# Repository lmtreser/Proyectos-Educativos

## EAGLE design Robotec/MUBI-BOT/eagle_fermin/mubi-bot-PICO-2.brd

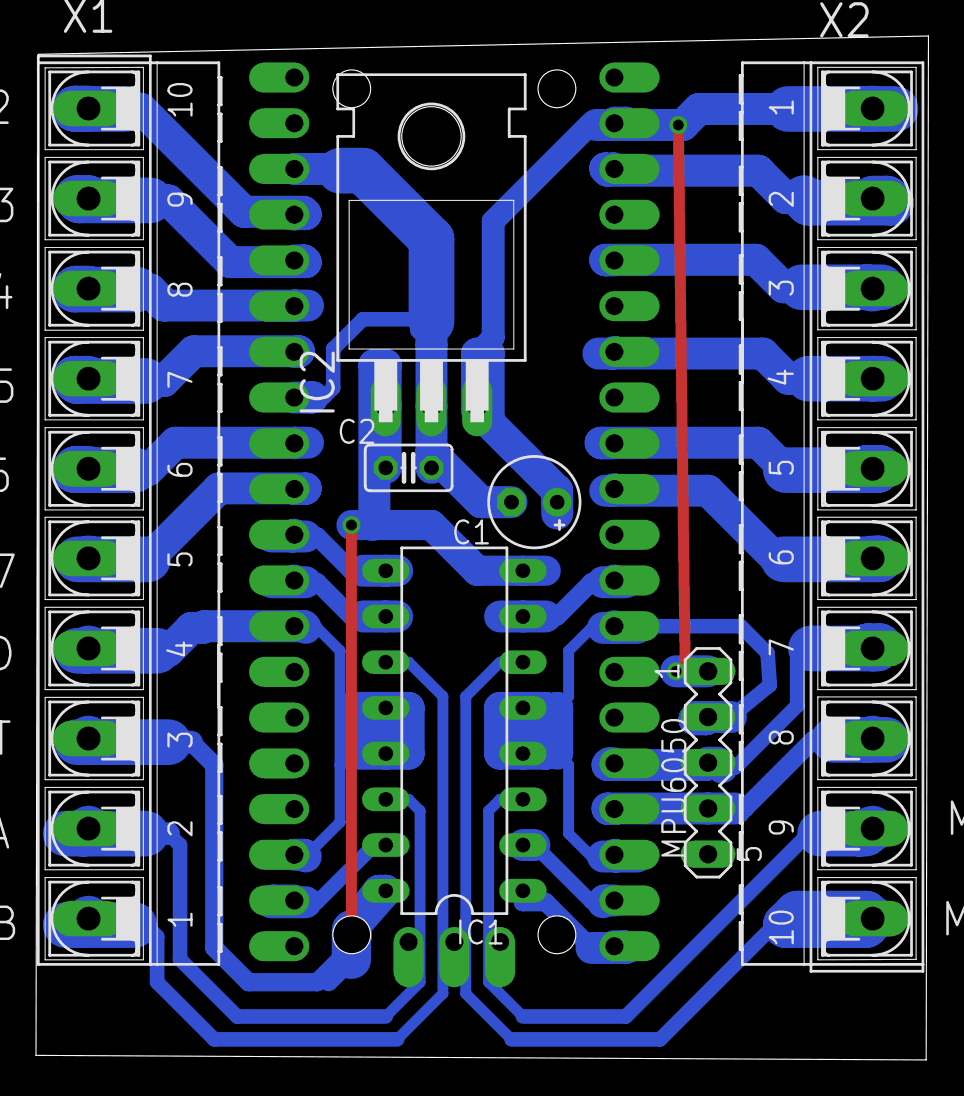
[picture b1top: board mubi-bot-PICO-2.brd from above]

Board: 2 copper layers, 49.6 x 56.9 mm, 8 parts (0 on the bottom side), 25 nets.

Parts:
C1: 10uF/16V; E2,5-5
C2: 100nF; C025-025X050
IC1: L293E; DIL16
IC2: 7805T; TO220H
MPU6050: MA05-1
U$2: RASPBERRY_PI_PICO_FOOTPRINT
X1, X2: AK500/10-H

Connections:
+3.3V: U$2.3V3(OUT), X2.3
+5V: C1.+, IC2.3, MPU6050.1, U$2.VSYS, X2.1
CM11: IC1.2, U$2.GP17
CM12: IC1.7, U$2.GP22
CM21: IC1.15, U$2.GP14
CM22: IC1.10, U$2.GP9
ENAM1: IC1.1, U$2.GP16
ENAM2: IC1.9, U$2.GP8
GND: C1.-, C2.2, IC1.4, IC1.5, IC1.12, IC1.13, IC2.2, MPU6050.2, U$2.GND@3, U$2.GND@8, U$2.GND@13, U$2.GND@18, U$2.GND@23, U$2.GND@28, U$2.GND@38, X1.4, X2.2
GP2: U$2.GP2, X1.10
GP3: U$2.GP3, X1.9
GP4: U$2.GP4, X1.8
GP5: U$2.GP5, X1.7
GP6: U$2.GP6, X1.6
GP7: U$2.GP7, X1.5
GP26: U$2.GP26_ADC0, X2.6
GP27: U$2.GP27_ADC1, X2.5
GP28: U$2.GP28_ADC2, X2.4
M1A: IC1.3, X2.9
M1B: IC1.6, X2.10
M2A: IC1.14, X1.2
M2B: IC1.11, X1.1
SCL: MPU6050.3, U$2.GP19, X2.7
SDA: MPU6050.4, U$2.GP18, X2.8
VBAT: C2.1, IC1.8, IC1.16, IC2.1, X1.3

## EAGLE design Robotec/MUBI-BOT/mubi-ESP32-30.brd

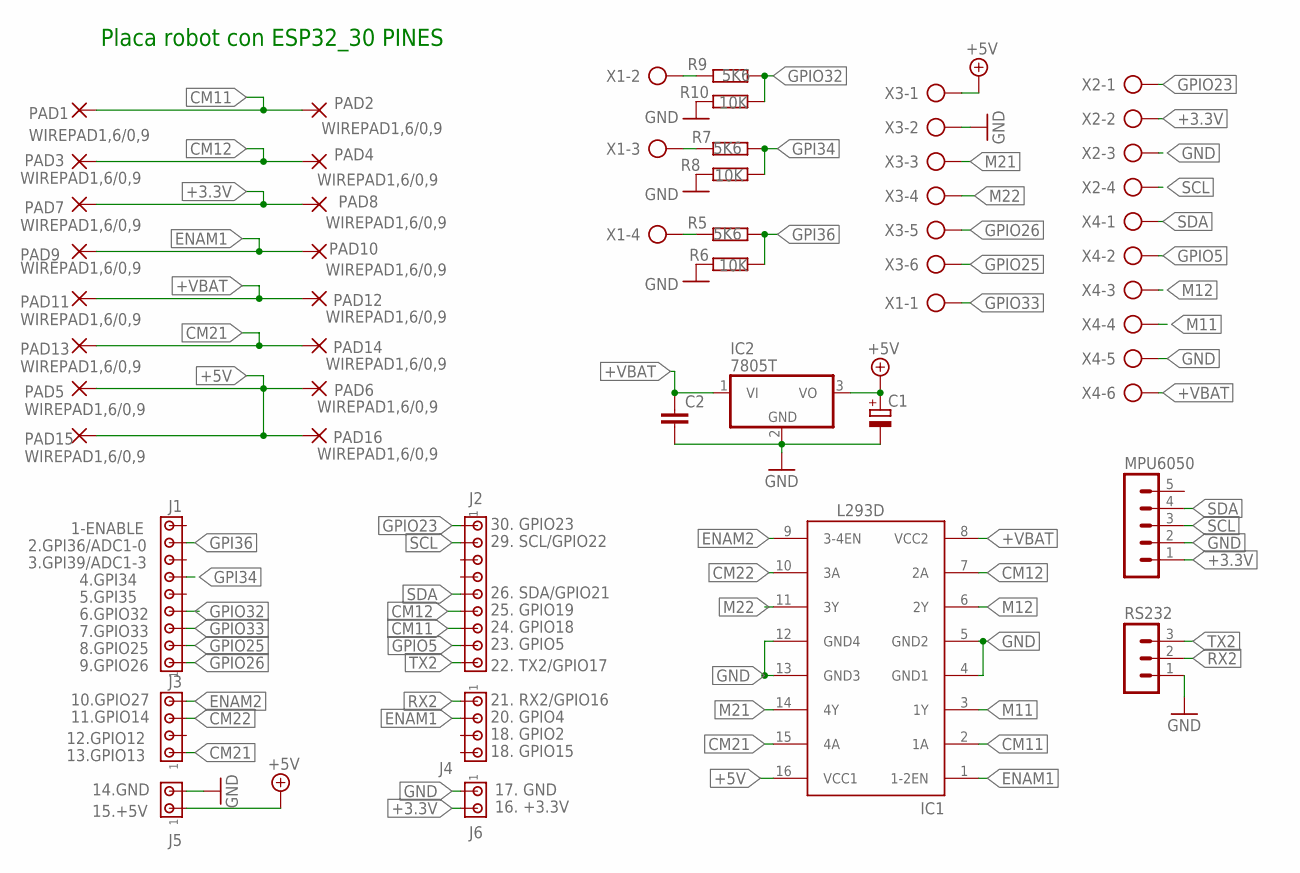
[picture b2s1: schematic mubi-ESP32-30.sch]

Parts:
C1: CPOL-EUE2.5-6; E2,5-6
C2: C-EU025-025X050; C025-025X050
IC1: L293D; DIL16
IC2: 7805T; TO220H
J1, J2: MTA09-100; 10X09MTA
J3, J4: MTA04-100; 10X04MTA
J5, J6: MTA02-100; 10X02MTA
MPU6050: MA05-1
PAD1, PAD2, PAD3, PAD4, PAD5, PAD6, PAD7, PAD8, PAD9, PAD10, PAD11, PAD12, PAD13, PAD14, PAD15, PAD16: WIREPAD1,6/0,9; 1,6/0,9
R5, R7, R9: 5K6; 0204/5
R6, R8, R10: 10K; 0204/5
RS232: MA03-1
X1, X2: AK500/4-H
X3, X4: AK500/6-H

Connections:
+3.3V: J6.2, MPU6050.1, PAD7.1, PAD8.1, X2.2
+5V: C1.+, IC1.16 (VCC1), IC2.3 (VO), J5.1, PAD5.1, PAD6.1, PAD15.1, PAD16.1, X3.1
+VBAT: C2.1, IC1.8 (VCC2), IC2.1 (VI), PAD11.1, PAD12.1, X4.6
CM11: IC1.2 (1A), J2.7, PAD1.1, PAD2.1
CM12: IC1.7 (2A), J2.6, PAD3.1, PAD4.1
CM21: IC1.15 (4A), J3.1, PAD13.1, PAD14.1
CM22: IC1.10 (3A), J3.3
ENAM1: IC1.1 (1-2EN), J4.2, PAD9.1, PAD10.1
ENAM2: IC1.9 (3-4EN), J3.4
GND: C1.-, C2.2, IC1.4 (GND1), IC1.5 (GND2), IC1.12 (GND4), IC1.13 (GND3), IC2.2 (GND), J5.2, J6.1, MPU6050.2, R6.2, R8.2, R10.2, RS232.1, X2.3, X3.2, X4.5
GPI34: J1.6, R7.2, R8.1
GPI36: J1.8, R5.2, R6.1
GPIO5: J2.8, X4.2
GPIO23: J2.1, X2.1
GPIO25: J1.2, X3.6
GPIO26: J1.1, X3.5
GPIO32: J1.4, R9.2, R10.1
GPIO33: J1.3, X1.1
M11: IC1.3 (1Y), X4.4
M12: IC1.6 (2Y), X4.3
M21: IC1.14 (4Y), X3.3
M22: IC1.11 (3Y), X3.4
unnamed: R5.1, X1.4
unnamed: R7.1, X1.3
unnamed: R9.1, X1.2
RX2: J4.1, RS232.2
SCL: J2.2, MPU6050.3, X2.4
SDA: J2.5, MPU6050.4, X4.1
TX2: J2.9, RS232.3

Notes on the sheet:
16. +3.3V
1-ENABLE
2.GPI36/ADC1-0
3.GPI39/ADC1-3
4.GPI34
5.GPI35
6.GPIO32
7.GPIO33
8.GPIO25
9.GPIO26
10.GPIO27
11.GPIO14
13.GPIO13
15.+5V
30. GPIO23
29. SCL/GPIO22
26. SDA/GPIO21
14.GND
25. GPIO19
24. GPIO18
22. TX2/GPIO17
21. RX2/GPIO16
20. GPIO4
Placa robot con ESP32_30 PINES
12.GPIO12
17. GND
18. GPIO15
18. GPIO2
23. GPIO5

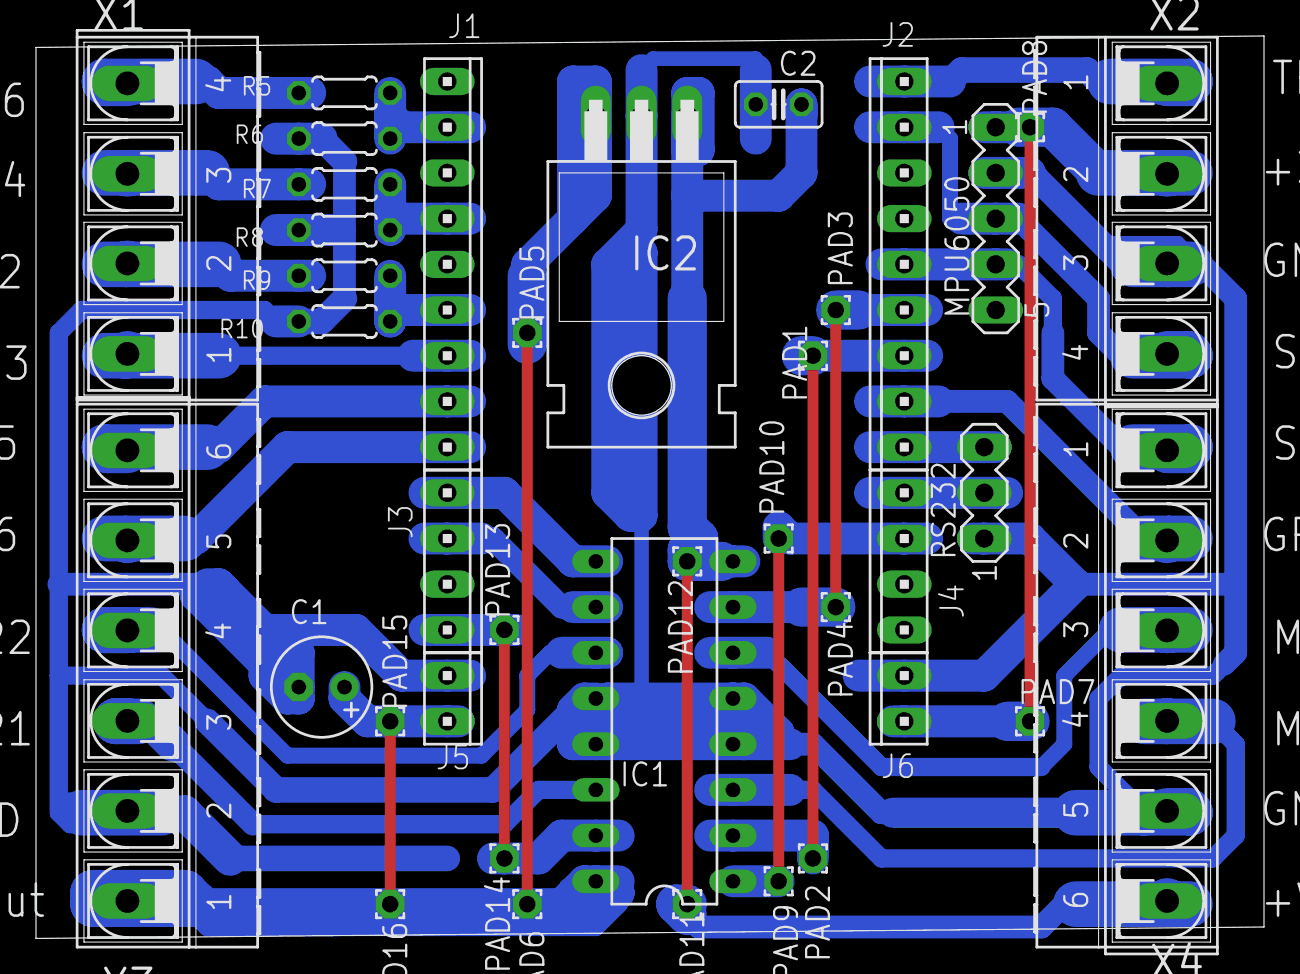
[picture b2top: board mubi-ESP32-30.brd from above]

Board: 2 copper layers, 68.2 x 50.2 mm, 38 parts (0 on the bottom side), 29 nets.

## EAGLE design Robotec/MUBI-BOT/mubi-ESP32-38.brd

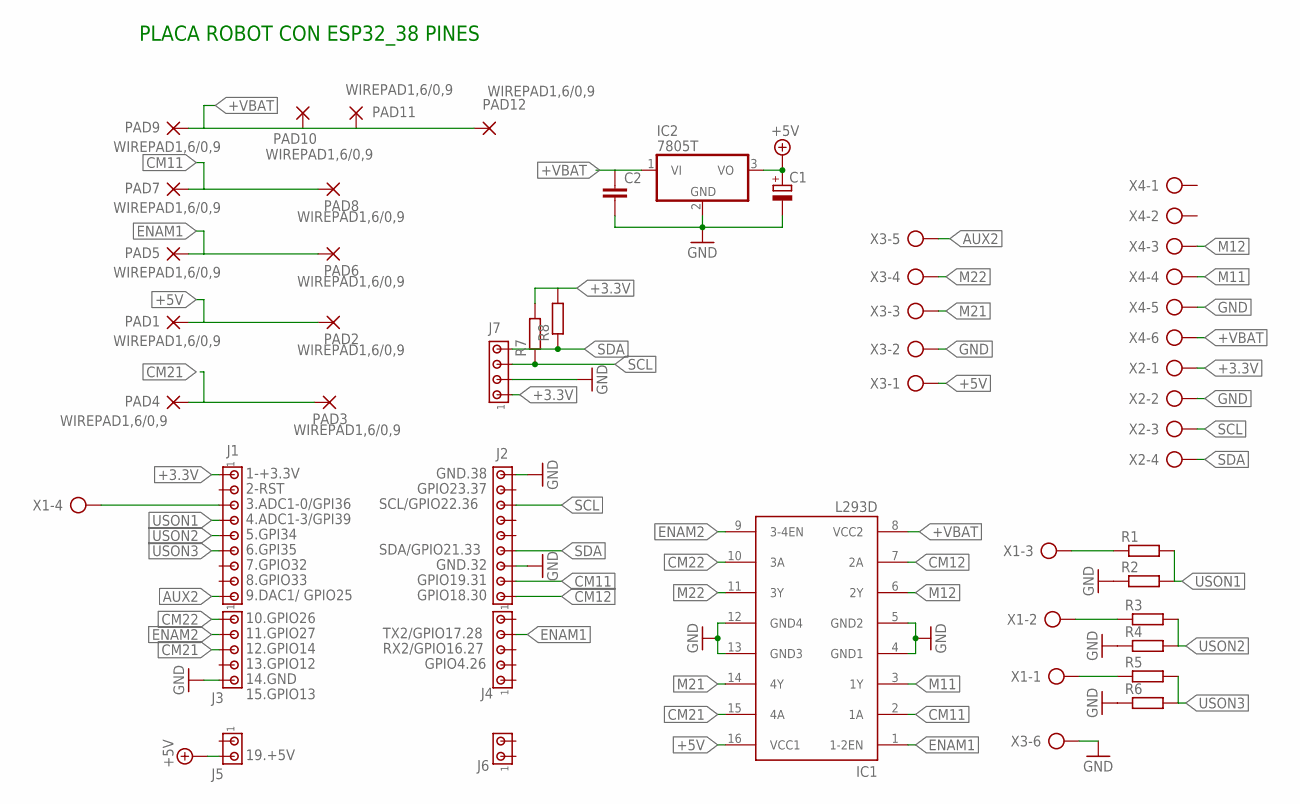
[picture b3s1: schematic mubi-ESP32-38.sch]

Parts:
C1: CPOL-EUE2.5-6; E2,5-6
C2: C-EU025-025X050; C025-025X050
IC1: L293D; DIL16
IC2: 7805T; TO220H
J1, J2: MTA09-100; 10X09MTA
J3, J4: MTA05-100; 10X05MTA
J5, J6: MTA02-100; 10X02MTA
J7: MTA04-100; 10X04MTA
PAD1, PAD2, PAD3, PAD4, PAD5, PAD6, PAD7, PAD8, PAD9, PAD10, PAD11, PAD12: WIREPAD1,6/0,9; 1,6/0,9
R1, R2, R3, R4, R5, R6: R-EU_0204/5; 0204/5
R7, R8: R-EU_0207/7; 0207/7
X1, X2: AK500/4-H
X3, X4: AK500/6-H

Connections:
+3.3V: J1.1, J7.1, R7.2, R8.2, X2.1
+5V: C1.+, IC1.16 (VCC1), IC2.3 (VO), J5.2, PAD1.1, PAD2.1, X3.1
+VBAT: C2.1, IC1.8 (VCC2), IC2.1 (VI), PAD9.1, PAD10.1, PAD11.1, PAD12.1, X4.6
AUX2: J1.9, X3.5
CM11: IC1.2 (1A), J2.2, PAD7.1, PAD8.1
CM12: IC1.7 (2A), J2.1
CM21: IC1.15 (4A), J3.3, PAD3.1, PAD4.1
CM22: IC1.10 (3A), J3.1
ENAM1: IC1.1 (1-2EN), J4.4, PAD5.1, PAD6.1
ENAM2: IC1.9 (3-4EN), J3.2
GND: C1.-, C2.2, IC1.4 (GND1), IC1.5 (GND2), IC1.12 (GND4), IC1.13 (GND3), IC2.2 (GND), J2.3, J2.9, J3.5, J7.2, R2.1, R4.1, R6.1, X2.2, X3.2, X3.6, X4.5
M11: IC1.3 (1Y), X4.4
M12: IC1.6 (2Y), X4.3
M21: IC1.14 (4Y), X3.3
M22: IC1.11 (3Y), X3.4
unnamed: R1.1, X1.3
unnamed: R3.1, X1.2
unnamed: R5.1, X1.1
unnamed: J1.3, X1.4
SCL: J2.7, J7.3, R7.1, X2.3
SDA: J2.4, J7.4, R8.1, X2.4
USON1: J1.4, R1.2, R2.2
USON2: J1.5, R3.2, R4.2
USON3: J1.6, R5.2, R6.2

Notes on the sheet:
1-+3.3V
2-RST
3.ADC1-0/GPI36
4.ADC1-3/GPI39
5.GPI34
6.GPI35
7.GPIO32
8.GPIO33
9.DAC1/ GPIO25
10.GPIO26
11.GPIO27
12.GPIO14
14.GND
15.GPIO13
19.+5V
GND.38
GPIO23.37
SCL/GPIO22.36
SDA/GPIO21.33
GND.32
GPIO19.31
GPIO18.30
TX2/GPIO17.28
RX2/GPIO16.27
GPIO4.26
PLACA ROBOT CON ESP32_38 PINES
13.GPIO12

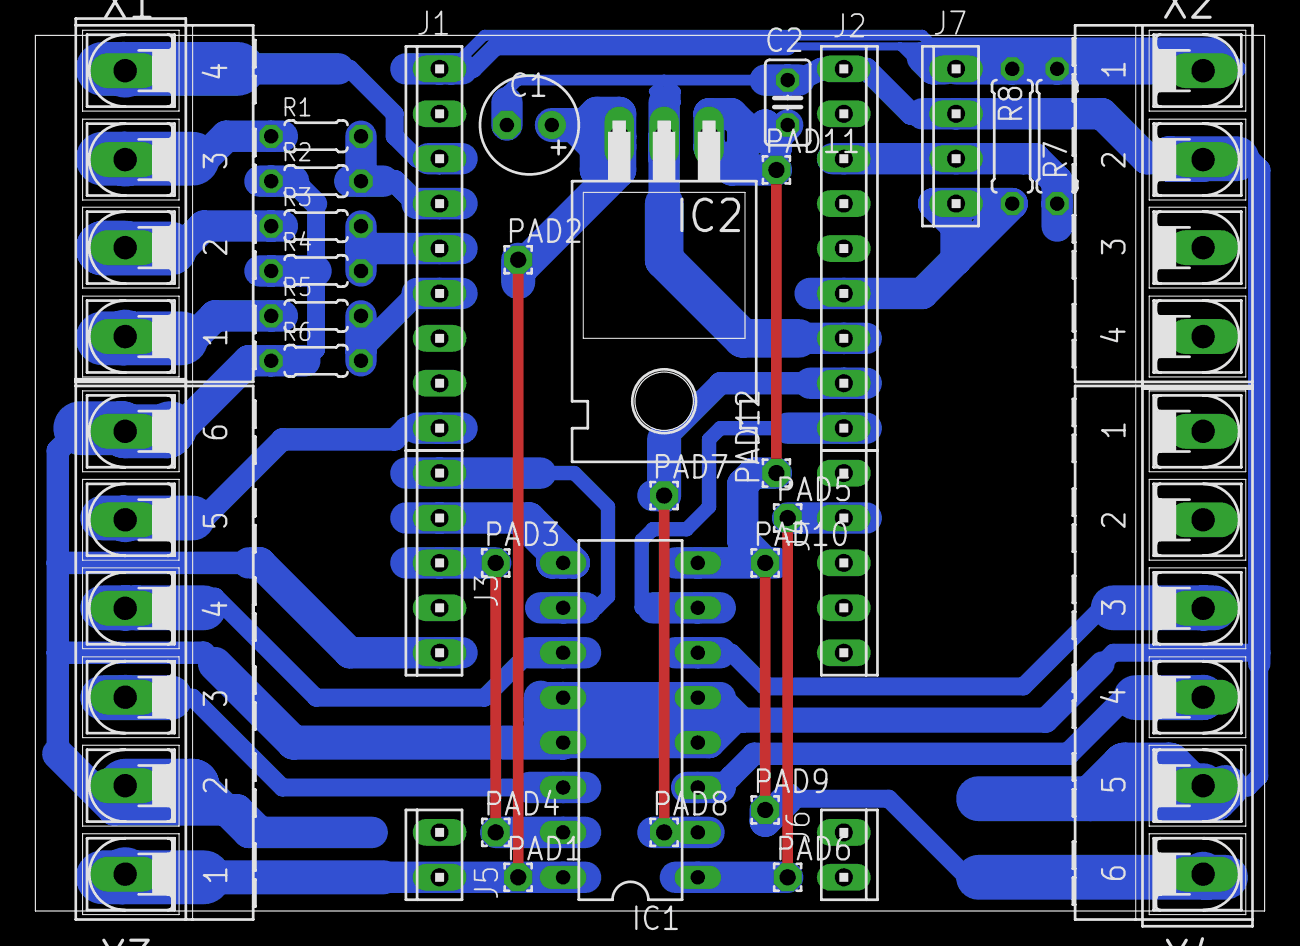
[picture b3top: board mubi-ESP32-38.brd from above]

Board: 2 copper layers, 69.5 x 49.5 mm, 35 parts (0 on the bottom side), 24 nets.

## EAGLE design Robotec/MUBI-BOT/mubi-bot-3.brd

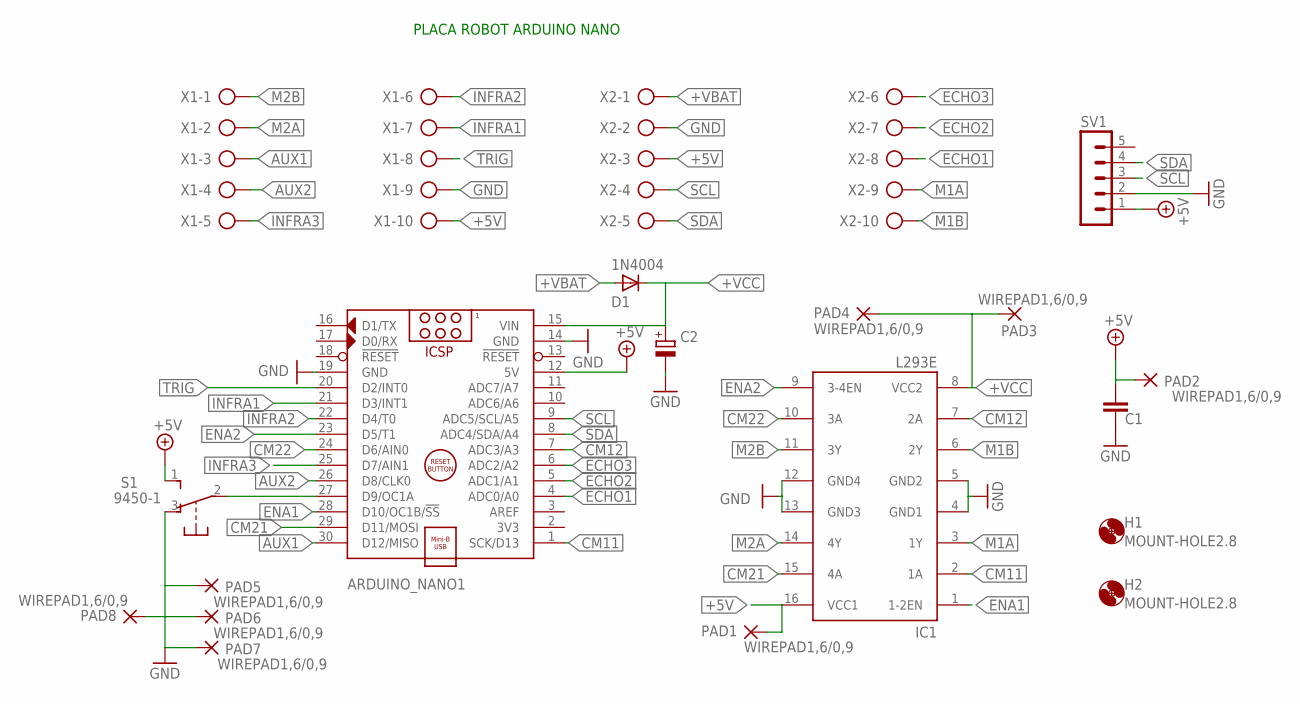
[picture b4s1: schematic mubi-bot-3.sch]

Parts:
ARDUINO_NANO1: ARDUINO_NANO
C1: C-EU050-025X075; C050-025X075
C2: CPOL-EUE2.5-5; E2,5-5
D1: 1N4004; DO41-10
H1, H2: MOUNT-HOLE2.8; 2,8
IC1: L293E; DIL16
PAD1, PAD2, PAD3, PAD4, PAD5, PAD6, PAD7, PAD8: WIREPAD1,6/0,9; 1,6/0,9
S1: 9450-1
SV1: MA05-1
X1, X2: AK500/10-H

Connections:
+5V: ARDUINO_NANO1.12 (5V), C1.1, IC1.16 (VCC1), PAD1.1, PAD2.1, S1.1 (S), SV1.1, X1.10, X2.3
+VBAT: D1.A, X2.1
+VCC: ARDUINO_NANO1.15 (VIN), C2.+, D1.C, IC1.8 (VCC2), PAD3.1, PAD4.1
AUX1: ARDUINO_NANO1.30 (D12/MISO), X1.3
AUX2: ARDUINO_NANO1.26 (D8/CLK0), X1.4
CM11: ARDUINO_NANO1.1 (SCK/D13), IC1.2 (1A)
CM12: ARDUINO_NANO1.7 (ADC3/A3), IC1.7 (2A)
CM21: ARDUINO_NANO1.29 (D11/MOSI), IC1.15 (4A)
CM22: ARDUINO_NANO1.24 (D6/AIN0), IC1.10 (3A)
ECHO1: ARDUINO_NANO1.4 (ADC0/A0), X2.8
ECHO2: ARDUINO_NANO1.5 (ADC1/A1), X2.7
ECHO3: ARDUINO_NANO1.6 (ADC2/A2), X2.6
ENA1: ARDUINO_NANO1.28 (D10/OC1B/!SS), IC1.1 (1-2EN)
ENA2: ARDUINO_NANO1.23 (D5/T1), IC1.9 (3-4EN)
GND: ARDUINO_NANO1.14 (GND), ARDUINO_NANO1.19 (GND), C1.2, C2.-, IC1.12 (GND4), IC1.13 (GND3), PAD5.1, PAD6.1, PAD7.1, PAD8.1, S1.3 (O), SV1.2, X1.9, X2.2
INFRA1: ARDUINO_NANO1.21 (D3/INT1), X1.7
INFRA2: ARDUINO_NANO1.22 (D4/T0), X1.6
INFRA3: ARDUINO_NANO1.25 (D7/AIN1), X1.5
M1A: IC1.3 (1Y), X2.9
M1B: IC1.6 (2Y), X2.10
M2A: IC1.14 (4Y), X1.2
M2B: IC1.11 (3Y), X1.1
unnamed: IC1.4 (GND1), IC1.5 (GND2)
unnamed: ARDUINO_NANO1.27 (D9/OC1A), S1.2
SCL: ARDUINO_NANO1.9 (ADC5/SCL/A5), SV1.3, X2.4
SDA: ARDUINO_NANO1.8 (ADC4/SDA/A4), SV1.4, X2.5
TRIG: ARDUINO_NANO1.20 (D2/INT0), X1.8

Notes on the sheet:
PLACA ROBOT ARDUINO NANO

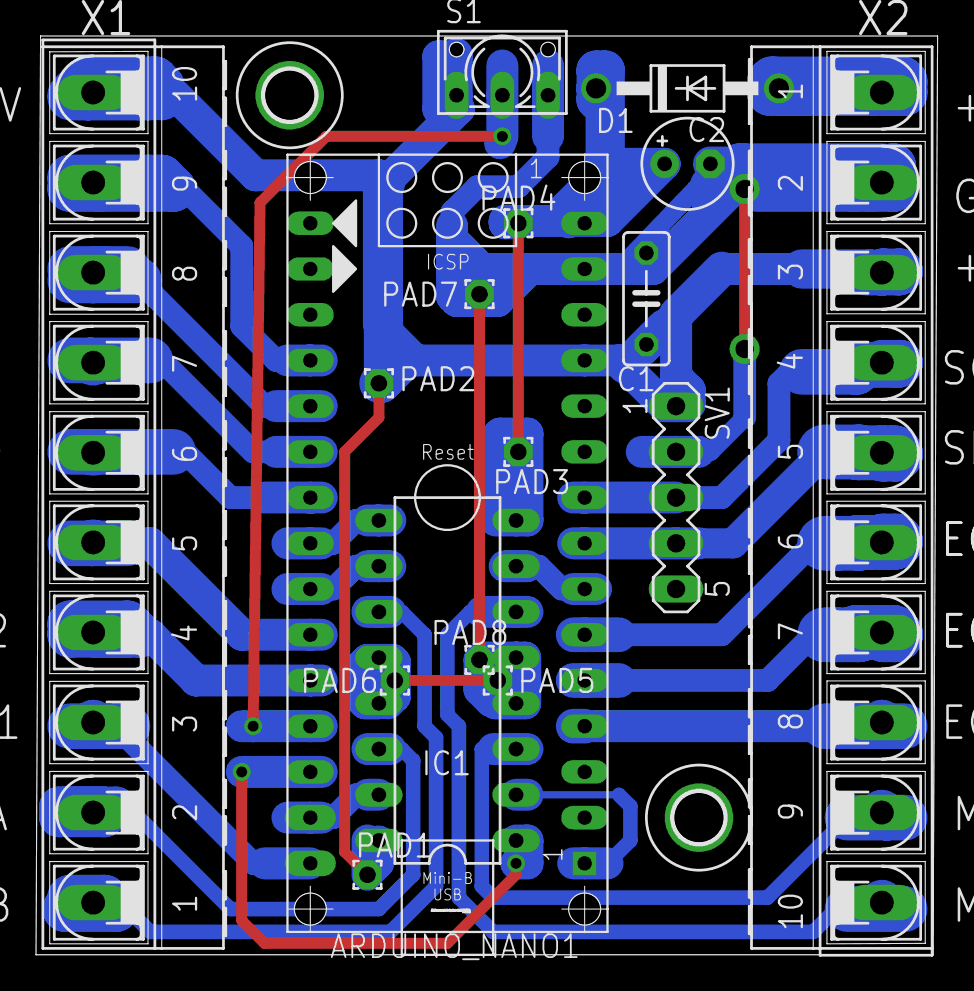
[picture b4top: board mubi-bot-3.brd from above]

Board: 2 copper layers, 50.1 x 51.0 mm, 19 parts (0 on the bottom side), 27 nets.
